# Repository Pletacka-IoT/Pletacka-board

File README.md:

# Pletacka-boad

## [Version 2.0](Pletacka-board-v2.0/README.md)

# [All photos](./Pletacka-board-v2.0/media/README.md)

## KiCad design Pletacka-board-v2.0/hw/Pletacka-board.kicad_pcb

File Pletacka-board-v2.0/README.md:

# Pletacka-boad v2.0

## Export manufacturing data - Linux

Run `make` in console 

### Required packages
 - [KiKit](https://github.com/yaqwsx/KiKit#installation) Automation for KiCAD
 - [Python 3](https://www.python.org/downloads/)

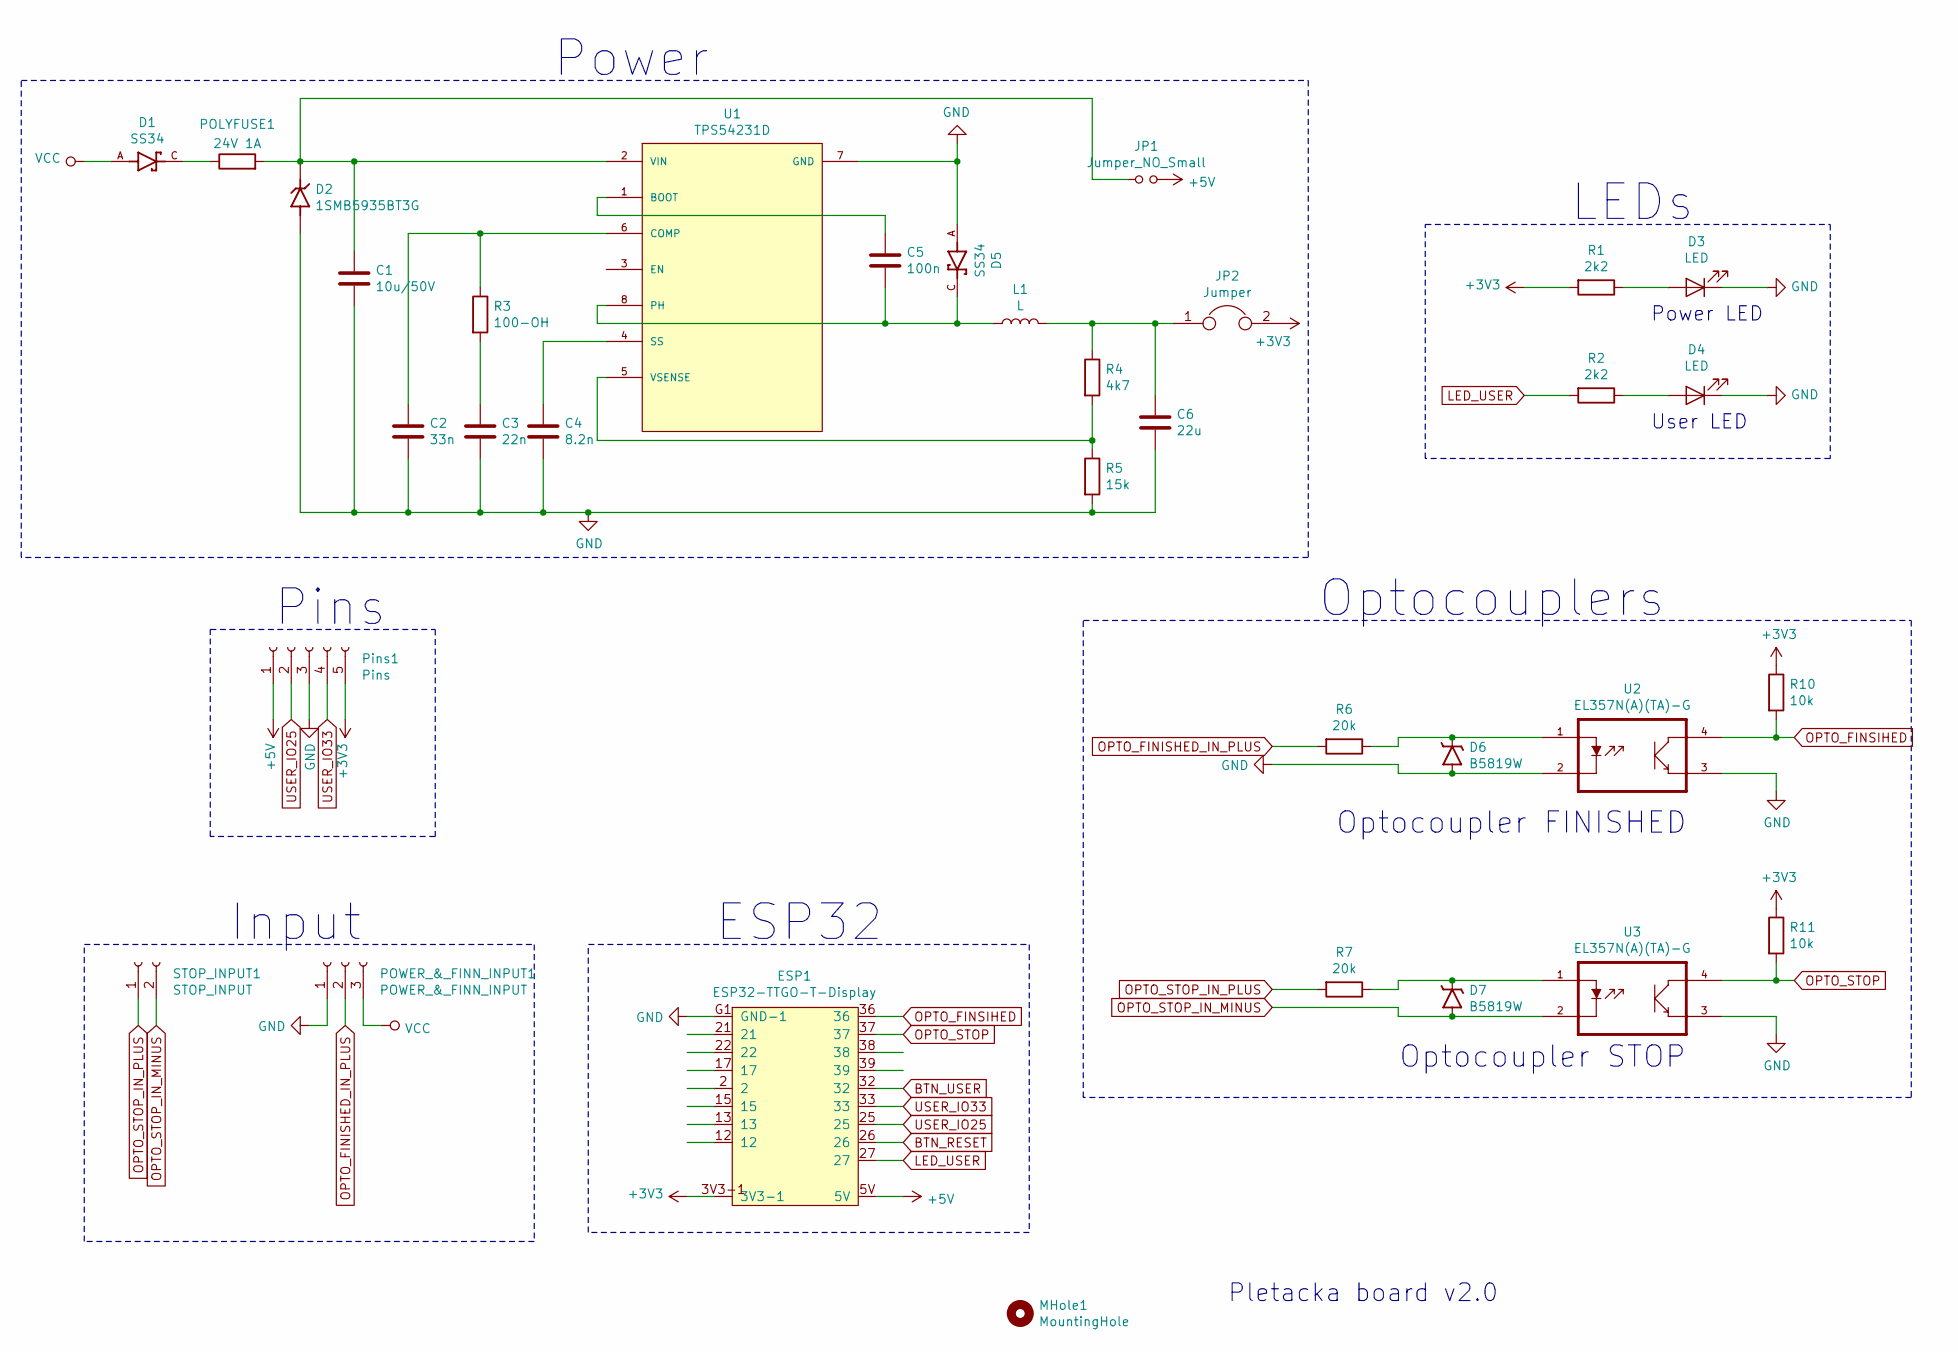
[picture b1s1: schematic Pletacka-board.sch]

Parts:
C1: 10u/50V; C_1206_3216Metric; LCSC C13585
C2: 33n; C_0603_1608Metric; LCSC C21117
C3: 22n; C_0603_1608Metric; LCSC C21122
C4: 8.2n; C_0603_1608Metric; LCSC C1032
C5: 100n; C_0603_1608Metric; LCSC C14663
C6: 22u; C_0603_1608Metric; LCSC C45783
D1, D5: SS34; SMA; LCSC C8678
D2: 1SMB5935BT3G; DIOM5436X247N; LCSC C49827
D3: LED; LED_0603_1608Metric; LCSC C72043
D4: LED; LED_0603_1608Metric; LCSC C2286
D6, D7: B5819W; B5819W_SOD-123; LCSC C8598
ESP1: ESP32-TTGO-T-Display
JP1: Jumper_NO_Small; SolderJumper-2_P1.3mm_Open_Pad1.0x1.5mm
JP2: Jumper; SolderJumper-2_P1.3mm_Bridged_Pad1.0x1.5mm
L1: L; SLW; LCSC C206321
MHole1: MountingHole; MountingHole_2.7mm_M2.5_Pad
POLYFUSE1: 24V 1A; R_1206_3216Metric; LCSC C70076
POWER_&_FINN_INPUT1: POWER_&_FINN_INPUT; TerminalBlock_Phoenix_PT-1,5-3-5.0-H_1x03_P5.00mm_Horizontal
Pins1: Pins; PinHeader_1x05_P2.54mm_Vertical
R1, R2: 2k2; R_0603_1608Metric; LCSC C4190
R3: 100-OH; R_0603_1608Metric; LCSC C22775
R4: 4k7; R_0603_1608Metric; LCSC C23162
R5: 15k; R_0603_1608Metric; LCSC C22809
R6, R7: 20k; R_0603_1608Metric; LCSC C4184
R10, R11: 10k; R_0603_1608Metric; LCSC C25804
STOP_INPUT1: STOP_INPUT; TerminalBlock_Phoenix_PT-1,5-2-5.0-H_1x02_P5.00mm_Horizontal
U1: TPS54231D; SOIC127P599X175-8N; LCSC C9865
U2, U3: EL357N(A)(TA)-G; SOP254P700X200-4N; LCSC C6649

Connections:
+3V3: ESP1.3V3-1, ESP1.3V3-2, JP2.2, Pins1.5, R1.2, R10.1, R11.1
+5V: ESP1.5V, JP1.2, Pins1.1
BTN_RESET: ESP1.26
BTN_USER: ESP1.32
GND: C1.2, C2.2, C3.2, C4.2, C6.2, D2.A, D3.1 (K), D4.1 (K), D5.A, D6.A, ESP1.G1 (GND-1), ESP1.G2 (GND-2), ESP1.G3 (GND-3), ESP1.G4 (GND-4), ESP1.G5 (GND-5), POWER_&_FINN_INPUT1.1, Pins1.3, R5.2, U1.7 (GND), U2.2, U2.3, U3.3
LED_USER: ESP1.27, R2.2
unnamed: C1.1, D2.C, JP1.1, POLYFUSE1.2, U1.2 (VIN)
unnamed: C2.1, R3.1, U1.6 (COMP)
unnamed: C3.1, R3.2
unnamed: C4.1, U1.4 (SS)
unnamed: C5.1, U1.1 (BOOT)
unnamed: C5.2, D5.C, L1.1, U1.8 (PH)
unnamed: C6.1, JP2.1, L1.2, R4.1
unnamed: D1.C, POLYFUSE1.1
unnamed: D3.2 (A), R1.1
unnamed: D4.2 (A), R2.1
unnamed: D6.C, R6.1, U2.1
unnamed: D7.C, R7.1, U3.1
unnamed: R4.2, R5.1, U1.5 (VSENSE)
OPTO_FINISHED_IN_PLUS: POWER_&_FINN_INPUT1.2, R6.2
OPTO_FINSIHED: ESP1.36, R10.2, U2.4
OPTO_STOP: ESP1.37, R11.2, U3.4
OPTO_STOP_IN_MINUS: D7.A, STOP_INPUT1.2, U3.2
OPTO_STOP_IN_PLUS: R7.2, STOP_INPUT1.1
USER_IO25: ESP1.25, Pins1.2
USER_IO33: ESP1.33, Pins1.4
VCC: D1.A, POWER_&_FINN_INPUT1.3

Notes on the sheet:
Input
Optocoupler FINISHED
Optocoupler STOP
Power
Optocouplers
ESP32
Pletacka board v2.0
Pins
User LED
Power LED
LEDs

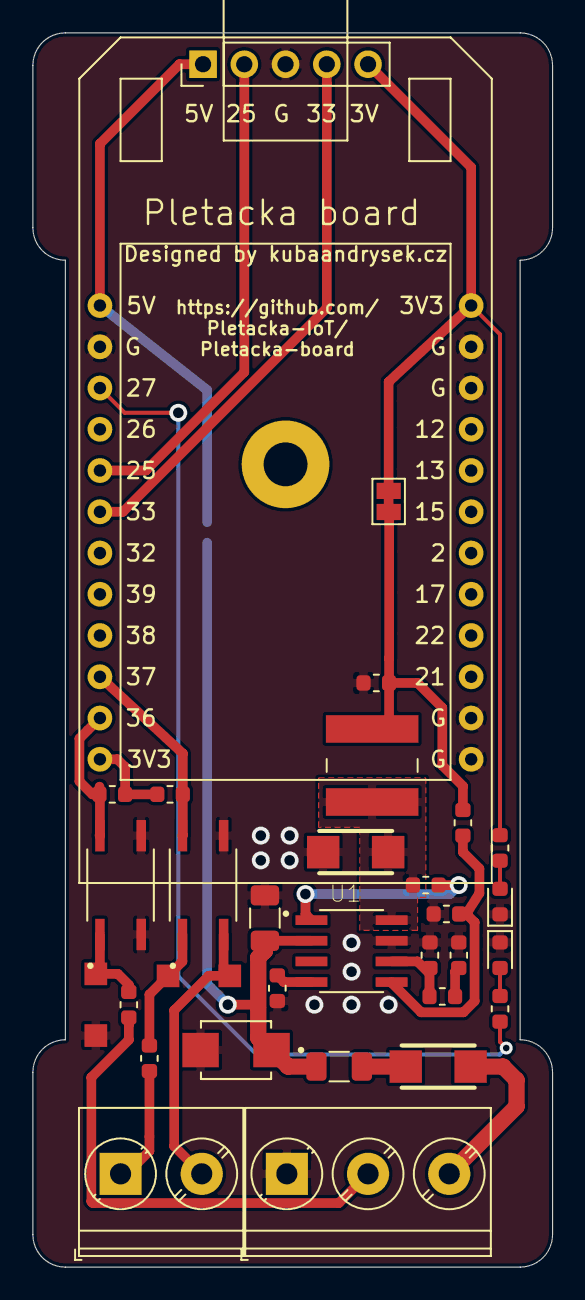
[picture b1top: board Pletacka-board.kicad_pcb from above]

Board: 2 copper layers, 32.0 x 76.0 mm, 34 parts (1 on the bottom side), 25 nets.

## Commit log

2020-06-18 Start creating board
2020-06-18 Add buttons and LEDs
2020-06-18 Add temperature sensor
2020-06-18 Remove old files
2020-06-19 Start routing
2020-06-19 One more time from start
2020-06-19 Start new project
2020-06-19 Add LEDs, RFID, Temp sen.
2020-06-19 Add Buttons + optocouplers
2020-07-23 Start power management
2020-07-27 cesgaw
2020-08-09 Route power supply
2020-08-09 Finish first routing
2020-08-09 Add 2 pinheads
2020-08-09 Fix Cednik's issues
2020-08-10 Start fixing
2020-08-10 Fix all atributes (fix #12)
2020-08-10 Change octocoupler resistor to 20k (close #2)
2020-08-10 Change step-down voltage (close #4)
2020-08-10 Change package of capacitor to 0805 (close #3)
2020-08-10 Edit buttons lables (close #16)
2020-08-10 Fix power supply routing (close #5 and close #6)
2020-08-10 Rename POWER to ON (close #7)
2020-08-10 Fix ON button schema name
2020-08-10 Add PS reverse polarity & over. pr. (close #8)
2020-08-11 Improve schema for step-down input
    - improve readability of over-voltage protection in schema
    - fix some minor issues (LCSC_IDs, ...)
2020-08-11 Fix Beware of tombstoning (close #9)
2020-08-11 Add JLCPCB order n. and tooling holes (close #11)
2020-08-11 Add pull-up resistors on I2C (close #14)
2020-08-11 Add input power voltage mesurement
2020-08-11 Move voltage mesurement resistors
2020-08-12 Update resistor R15
2020-08-12 Update Polyfuse atribute
2020-08-12 Fix ports rotation
2020-10-16 Start new version 2.0 in Kicad
2020-10-16 Create ESP32-TTGO library
2020-10-16 Add gitignore
2020-10-16 Add files
2020-10-16 Add octocoupler library
2020-10-17 Add libraries
2020-10-17 Add connectors
2020-10-17 Update some packages, add 3D models
2020-10-18 Update some packages
2020-10-18 Routing schema
2020-10-18 Routing board
2020-10-18 Add Kicad project file
2020-10-18 Update improve schema and broke board
2020-10-18 Remove blank sheets
2020-10-19 New routing of board
2020-10-19 Change buttons and fill ground
2020-10-19 Repair files problem
2020-10-19 Add Kuba Logo
2020-10-19 Fix small issues
2020-10-19 Change Inductor
2020-10-19 Testin fabrication export
2020-10-21 Finish board
2020-10-21 Add pictures, update redme
2020-10-24 Change file structure & add old version 1.0
2020-10-25 Add software v1
2020-10-25 Change file name - software v1.0
2020-10-25 Add sw v2
2020-10-25 Update to new version of display library
2020-10-25 Remove buttons - chage board
2020-10-25 Add export to gitignore
2020-10-25 Add new version 1.0.1
2020-10-25 Fix multiple files include
2020-10-25 Run GridUI from main.c
2020-10-25 Move GridUI to Pletacka
2020-10-26 Add sensor number change by gridUI
2020-10-26 Testing v1.0.2
2020-10-26 Add UI - Protocol
2020-10-26 Repair main
2020-10-26 Fix Board tester
2020-10-26 Improveing GridUI View
2020-10-28 Add few versions
2020-10-29 Add stable version
2020-11-13 New stable version
2020-11-15 Fix Layoyt sending
2020-11-15 Fix Config file name
2020-12-12 Add cover, SW-v2.0
2020-12-12 New set ID button, change behavior
2020-12-15 Nice schema
2021-02-27 Add v2.0.2 (fix display, add speed)
2022-10-15 Update gitignore
